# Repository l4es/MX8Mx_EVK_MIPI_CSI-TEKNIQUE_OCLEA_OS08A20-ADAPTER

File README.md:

# MX8Mx_EVK_MIPI_CSI-TEKNIQUE_OCLEA_OS08A20-ADAPTER
Adapter for interfacing Teknique's Oclea OS08a20 to MX8M Mini/Plus EVK

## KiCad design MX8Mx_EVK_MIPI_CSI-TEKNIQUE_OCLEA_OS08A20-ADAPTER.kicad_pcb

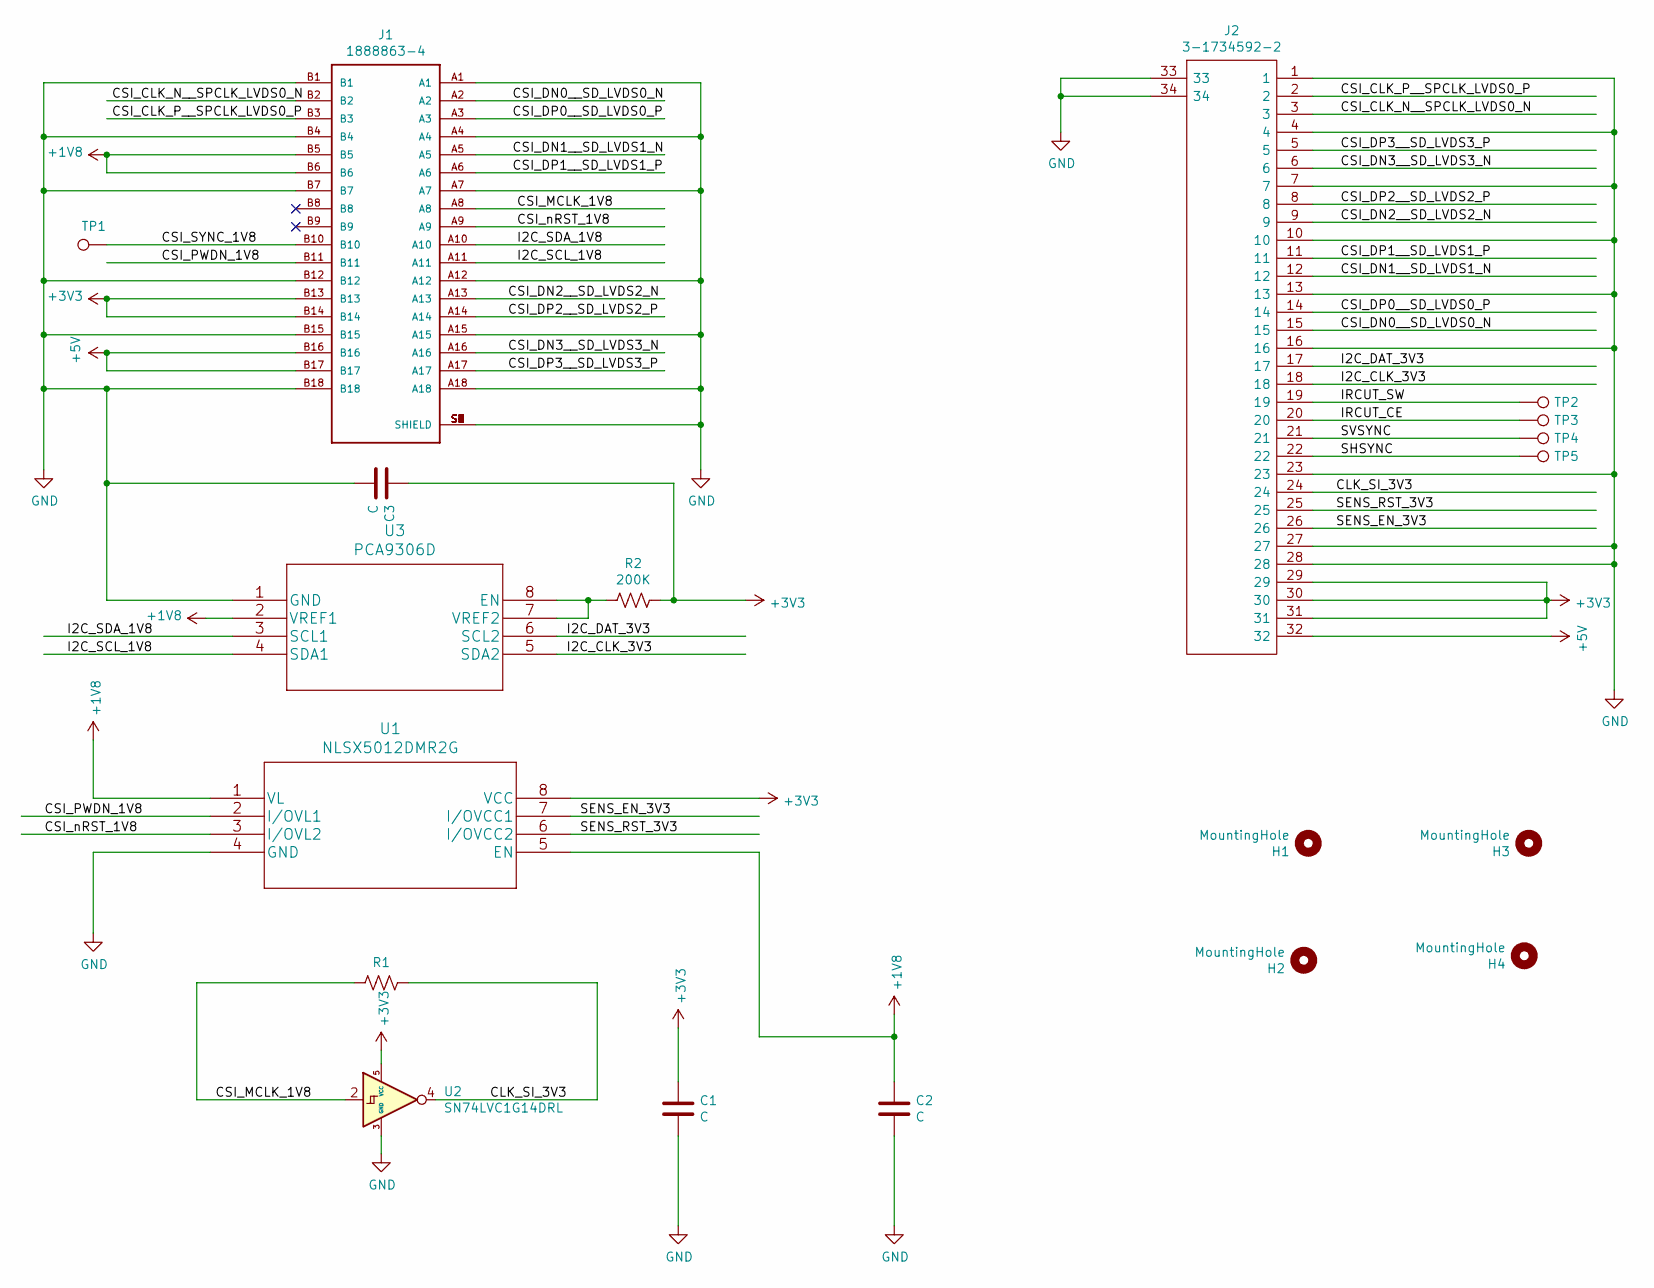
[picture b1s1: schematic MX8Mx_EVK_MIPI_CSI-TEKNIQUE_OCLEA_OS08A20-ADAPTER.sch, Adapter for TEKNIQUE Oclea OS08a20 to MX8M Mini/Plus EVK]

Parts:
C1, C2, C3: C; C_0603_1608Metric_Pad1.08x0.95mm_HandSolder
H1, H2, H3, H4: MountingHole; MountingHole_2.2mm_M2_Pad
J1: 1888863-4; TE_1888863-4
J2: 3-1734592-2; 317345922; Manufacturer_Part_Number 3-1734592-2; Mouser Part Number 571-3-1734592-2
R1: R_US; R_0805_2012Metric_Pad1.20x1.40mm_HandSolder
R2: 200K; R_0805_2012Metric_Pad1.20x1.40mm_HandSolder
TP1, TP2, TP3, TP4, TP5: TestPoint; TestPoint_Pad_D1.0mm
U1: NLSX5012DMR2G
U2: SN74LVC1G14DRL; SOT-553
U3: PCA9306D

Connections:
+1V8: C2.1, J1.B5, J1.B6, U1.1 (VL), U1.5 (EN), U3.2 (VREF1)
+3V3: C1.1, C3.1, J1.B13, J1.B14, J2.29, J2.30, J2.31, R2.1, U1.8 (VCC), U2.5 (VCC)
+5V: J1.B16, J1.B17, J2.32
/CLK_SI_3V3: J2.24, R1.1, U2.4
/CSI_CLK_N__SPCLK_LVDS0_N: J1.B2, J2.3
/CSI_CLK_P__SPCLK_LVDS0_P: J1.B3, J2.2
/CSI_DN0__SD_LVDS0_N: J1.A2, J2.15
/CSI_DN1__SD_LVDS1_N: J1.A5, J2.12
/CSI_DN2__SD_LVDS2_N: J1.A13, J2.9
/CSI_DN3__SD_LVDS3_N: J1.A16, J2.6
/CSI_DP0__SD_LVDS0_P: J1.A3, J2.14
/CSI_DP1__SD_LVDS1_P: J1.A6, J2.11
/CSI_DP2__SD_LVDS2_P: J1.A14, J2.8
/CSI_DP3__SD_LVDS3_P: J1.A17, J2.5
/CSI_MCLK_1V8: J1.A8, R1.2, U2.2
/CSI_PWDN_1V8: J1.B11, U1.2 (I/OVL1)
/CSI_SYNC_1V8: J1.B10, TP1.1
/CSI_nRST_1V8: J1.A9, U1.3 (I/OVL2)
/I2C_CLK_3V3: J2.18, U3.5 (SDA2)
/I2C_DAT_3V3: J2.17, U3.6 (SCL2)
/I2C_SCL_1V8: J1.A11, U3.4 (SDA1)
/I2C_SDA_1V8: J1.A10, U3.3 (SCL1)
/IRCUT_CE: J2.20, TP3.1
/IRCUT_SW: J2.19, TP2.1
/SENS_EN_3V3: J2.26, U1.7 (I/OVCC1)
/SENS_RST_3V3: J2.25, U1.6 (I/OVCC2)
/SHSYNC: J2.22, TP5.1
/SVSYNC: J2.21, TP4.1
GND: C1.2, C2.2, C3.2, J1.A1, J1.A4, J1.A7, J1.A12, J1.A15, J1.A18, J1.B1, J1.B4, J1.B7, J1.B12, J1.B15, J1.B18, J1.S1 (SHIELD), J1.S2 (SHIELD), J1.S3 (SHIELD), J1.S4 (SHIELD), J1.S5 (SHIELD), J1.S6 (SHIELD), J1.S7 (SHIELD), J1.S8 (SHIELD), J2.1, J2.4, J2.7, J2.10, J2.13, J2.16, J2.23, J2.27, J2.28, J2.33, J2.34, U1.4 (GND), U2.3 (GND), U3.1 (GND)
unnamed: R2.2, U3.7 (VREF2), U3.8 (EN)

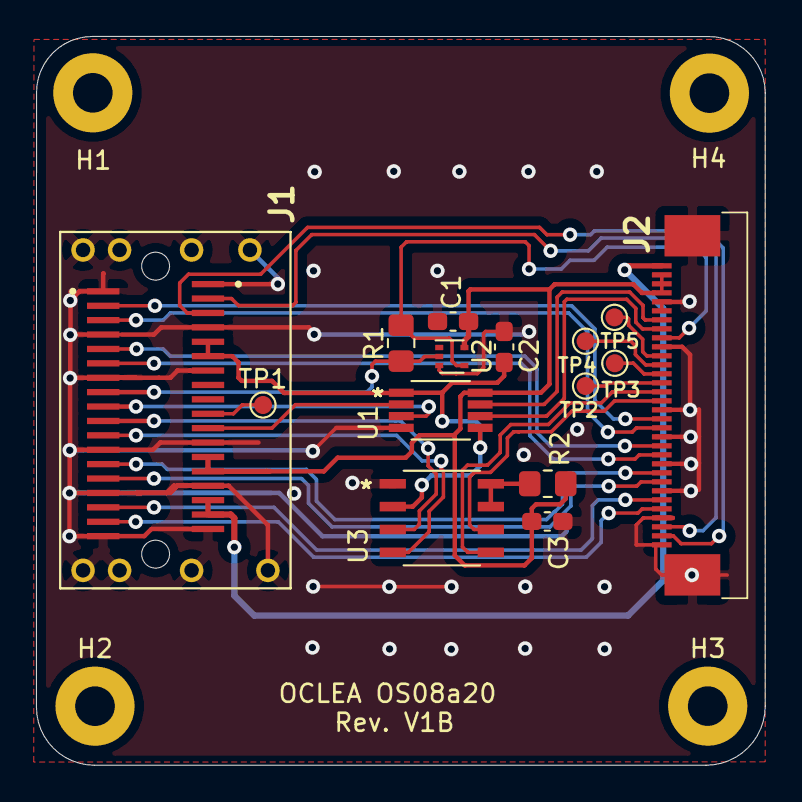
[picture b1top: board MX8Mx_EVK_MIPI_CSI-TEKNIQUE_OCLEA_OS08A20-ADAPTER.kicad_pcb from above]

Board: 2 copper layers, 40.5 x 40.5 mm, 19 parts (0 on the bottom side), 30 nets.

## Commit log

2021-08-06 Completed layout (J1 might need to be Y mirrored)
2021-08-07 Mirror J1 signals (A-side to B-side and vice-versa) for mating with the MIPI-CSI interface(s) on EVK
2021-08-07 Change 32-pin connector from Omron XF2M-3215-1A to TE 3-1734592-2
2021-08-07 Add round-corners
2021-08-07 Add first production release V1A
2021-11-10 MX8Mx_EVK_MIPI_CSI-TEKNIQUE_OCLEA_OS08A20-ADAPTER.sch : Edit title block (title, date, revision)
2021-11-10 Update V1A revision
2021-11-10 Update components' libraries
2021-11-11 Update design with separate I2C and GPIO level translators
2021-11-11 Complete routing of new design with separate I2C and GPIO level translators
2021-12-12 Add production data for release V1B
2021-12-12 Add documentation
2021-12-12 Add README with illustration

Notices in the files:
parts and their libraries:
Copyright 2021 Accelerated Designs. All rights reserved.
